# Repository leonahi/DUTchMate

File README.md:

# DUTchMate

DUTchMate helps embedded developers turn UART output and hardware-control
actions into durable evidence that humans and coding agents can inspect. Its
local Device Core Service continuously records UART while it owns a connected
backend. The CLI and service expose deterministic atomic capabilities;
clients and coding agents compose higher-level debug procedures from them.

- **Continuous evidence recording** preserves UART between client requests.
- **Audited Control** provides configured reset, boot-mode, and GPIO actions,
  with durable attempt evidence before physical dispatch.
- **Monitor** observes new evidence for a bounded duration or until a condition.
- **Interact** sends exact UART bytes once and observes a bounded response window.
- **Audited UART TX** sends standalone payloads with explicit line-ending behavior.

## What it looks like

Configure the DUT I/O voltage in the project profile and connect an RP2350-based
Debug Helper. The Enhanced backend can discover and open it during startup.
Configure the reset signal, then use separate Control and observation requests:

```bash
dutchmate devices
dutchmate start --backend enhanced
dutchmate gpio mode CTRL0 reset RESET_N \
  --mode open_drain --active-level low
dutchmate dut reset
dutchmate monitor --seconds 15
dutchmate logs --last 100
```

An illustrative Monitor result identifies its bounded evidence window:

```text
Monitor elapsed
Operation: monitor-00000000-0000-4000-8000-000000000001
Evidence: 20261025T120000Z-demo0001:0..12
```

Recording is already active before reset. A later Monitor observes only evidence
after its own start; immediate boot output remains in the session and is available
through log retrieval. These are independent atomic requests, with no dedicated
reset-and-observe workflow in Device Core.

With `[hardware.uart].tx_enabled = true`, ordinary UART interaction uses the
same service-owned connection and evidence journal:

```bash
dutchmate monitor --until BOOT_OK --timeout 10
dutchmate send PING --line-ending lf
dutchmate send --data-b64 AP8=
dutchmate interact INFO --line-ending lf --until 'DMF/1 INFO' --timeout 5
dutchmate follow                  # Ctrl-C detaches the view; recording continues
dutchmate console --line-ending lf
dutchmate sessions
dutchmate session SESSION_ID
dutchmate release                 # external same-port tool may now open the port
# Close the external tool before reacquiring.
dutchmate reacquire
```

Monitor/Interact return operation IDs and evidence ranges; finishing an operation
leaves the continuous session active. Release/reacquire records the unobserved
interval and opens a fresh timestamp segment. `capture` and `wait` are thin
Monitor aliases. New evidence uses schema v2; historical v0/v1 sessions remain
readable. The Debug Agent currently accepts schema-v1 evidence only.

Coding agents can use the CLI or service to compose procedures from Monitor,
Interact, audited UART TX, and audited reset/boot/GPIO Control. UART TX requires
the profile's TX policy to be enabled. The local stdio MCP adapter exposes the
[twelve-tool v2 catalog](docs/mcp_integration_plan.md#target-tool-catalog), including
Monitor, Interact, configured reset/boot Control and evidence retrieval. It is a
thin HTTP client of the already-running Device Core Service; it never starts the
service or acquires the serial port. Register the installed `dutchmate-mcp` or
`dutchmate mcp` command using the [developer guide](docs/developer_guide.md#register-mcp-with-a-coding-agent).

## Install

DUTchMate requires Python 3.10 or newer. The examples on this page describe the
current checkout. Install its workspace and make its commands available in the
current shell:

```bash
uv sync --all-packages
export PATH="$PWD/.venv/bin:$PATH"
```

For the published `v0.1.0` release, use either isolated-tool installer below.
That release predates the Phase 1/MCP v2 migrations; its original surface is
described in the [historical release notes](docs/releases/v0.1.0.md). The workspace
package version alone does not mean these checkout changes have been published.

```bash
uv tool install dutchmate==0.1.0
# or
pipx install dutchmate==0.1.0
```

## Quick Start

For Enhanced, set `[hardware].dut_io_voltage` in `.dutchmate/config.toml` to
the actual DUT logic voltage before opening the Debug Helper. List candidate
devices, start one backend, inspect it, and stop the service:

```bash
dutchmate devices
dutchmate start --backend enhanced
dutchmate status
dutchmate stop
```

Basic mode requires a user-selected generic USB-to-UART port. Enhanced mode can
auto-select one metadata-hinted Debug Helper; multiple candidates require an
explicit port. Run `dutchmate --help` for the complete command surface and see
the [developer guide](docs/developer_guide.md) for configuration and MCP host
registration.

For Basic, replace the start command with
`dutchmate start --backend basic --serial-port /dev/cu.EXAMPLE`, using the
actual adapter path. Select one backend at a time.

## Hardware

The **Basic** backend uses a generic TTL/logic-level USB-to-UART adapter for UART
receive and optional UART send. The **Enhanced** backend uses the RP2350-based
Raspberry Pi Pico 2 Debug Helper for UART receive/send, device timestamps,
buffer telemetry, and generic `CTRLn` control. Both feed the same host session
pipeline, but they are mutually exclusive selections; hybrid operation is not
supported.

## Contributing / Development

Start with the [current development status](docs/development_status.md), which
owns active progress and next steps. Completed work is preserved in the
[development history](docs/development_history.md). Setup and validation live
in the [developer guide](docs/developer_guide.md); the full
[documentation index](docs/README.md) and [glossary](docs/glossary.md) cover the
remaining project contracts.

The repository is a `uv` workspace. From a checkout:

```bash
uv sync --all-packages
uv run pytest
uv run ruff check .
```

## Licensing and contributions

Unless otherwise noted, DUTchMate software, firmware, protocol definitions,
documentation, scripts, and supporting tools are licensed under the
[MIT License](LICENSE).

DUTchMate-authored hardware design files under `hardware/pcb/` are licensed
under [CERN-OHL-P-2.0](LICENSES/CERN-OHL-P-2.0.txt). Third-party components
retain their respective licenses. The legacy EAGLE files and third-party CAD
assets retain their existing terms; see [LICENSE.md](LICENSE.md) for the scope
and [third-party notices](THIRD_PARTY_NOTICES.md).

The DUTchMate name, logo, and associated branding are excluded from these
grants. The MIT License and CERN-OHL-P-2.0 do not grant permission to use them
to identify or promote derivative products as official DUTchMate products.

Future pull-request commits require DCO 1.1 sign-off. See
[CONTRIBUTING.md](CONTRIBUTING.md) for the contribution and validation workflow.

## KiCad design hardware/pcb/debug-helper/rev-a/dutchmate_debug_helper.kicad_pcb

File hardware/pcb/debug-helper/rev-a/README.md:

# Debug Helper Revision A — KiCad source

This directory contains the current authoritative Rev-A KiCad design source
for the DUTchMate Debug Helper. The historical EAGLE prototype design record
is preserved separately under [legacy-eagle](../legacy-eagle/revision_a.md).
Its component references and connector assignments do not define this KiCad
implementation.

## Design sources

- `dutchmate_debug_helper.kicad_pro`: KiCad project and check settings.
- `dutchmate_debug_helper.kicad_sch`: schematic and embedded symbol definitions.
- `dutchmate_debug_helper.kicad_pcb`: board source.
- `dutchmate_debug_helper.kicad_dru`: project design rules.
- `libraries/symbols/dutchmate.kicad_sym`: project-owned logic and analog-switch
  symbol definitions, resolved through `sym-lib-table` using `${KIPRJMOD}`.

The sources use KiCad 10 format. Standard KiCad symbols and footprints must be
installed alongside the project-owned library. Keep editable sources and any
reviewed manufacturing outputs in version control; local settings, locks,
autosaves, backups, and scratch exports are ignored.

## Electrical architecture and agreed corrections

The helper uses a non-wireless Raspberry Pi Pico 2 / RP2350 module (`A1`),
with a 3.3 V helper domain, a DUT-supplied `DUT_VIO` reference of 1.8–5.0 V,
and common ground. `DUT_VIO` supplies the interface circuitry; it is not an
output for powering the DUT.

| Block | KiCad implementation |
|---|---|
| Four control outputs | `U1 SN74LV4T125`, VCC=`DUT_VIO`; `U7/U8 SN74LVC2G06` open-drain enable drivers powered by `+3.3V` |
| Control data defaults | `R14–R17`, 10 kΩ to GND on `DBG_CTRL_DATA0–3` |
| Control enable defaults | `R1–R4`, 4.7 kΩ to GND; active-low `DBG_CTRL_OE0_N–3_N` pulled to `DUT_VIO` by `R7/R6/R9/R8`, respectively, each 4.7 kΩ |
| Four event inputs | `U5 TXU0104PWR`, VCCA=`DUT_VIO`, VCCB=`+3.3V`; `R5=4.7 kΩ` pulls `DBG_INPUT_IF_EN` low |
| UART | `U2 TXU0202DCUR`, VCCA=`+3.3V`, VCCB=`DUT_VIO`; `R12=4.7 kΩ` pulls `DBG_UART_IF_EN` low |
| Series resistance | `RN3/RN4=180 Ω` for control/event channels; `RN5=22 Ω` for UART |
| Protection | `U6` on connector-side controls, `U4` on connector-side events/UART, `D1` between `DUT_VIO` and GND |

The 4.7 kΩ enable pull-downs retain compatibility with older RP2350 A2
silicon; the design does not require A4-only modules. Control data pull-downs
define the buffer inputs while Pico GPIOs are undriven. The independent `/OE`
paths determine DUT-facing Hi-Z, including open-drain release. Push-pull and
open-drain control modes still require the appropriate firmware data/enable
sequence.

### Hardware-defined DUT_VIO sense isolation

`U3 TMUX2819DSGR` is connected as follows:

| Pin | Connection |
|---|---|
| 1, SA | `DUT_VIO` |
| 2, NC | GND, as specified by the datasheet |
| 3, EN; 8, VDD | `+3.3V`, with `C16=100 nF` between VDD and GND |
| 4, GND; 9, exposed pad | GND |
| 5, SB | Intentionally unconnected |
| 6, D | `R10` divider input |
| 7, SEL | GND |

With helper power present, EN high and SEL low select SA. With VDD absent,
the switch provides powered-off isolation within its specified leakage limits.
No firmware GPIO controls this isolation. The selected switch supports DUT
signals above its 3.3 V supply within the specified signal range. See the
[TMUX2819 datasheet](https://www.ti.com/lit/ds/symlink/tmux2819.pdf).

The divider remains `R10=47 kΩ` and `R11=47 kΩ`, with `C7=10 nF` from
`DUT_VIO_SENSE` to `GNDA`. `R11` also returns to `GNDA`, connected to the
Pico's AGND pin 33. `DUT_VIO_SENSE` reaches GP28/ADC2, module pin 34. The Pico
module supplies the internal analog/common-ground connection; these are
distinct carrier-board net names, not galvanically isolated domains.

GP28 ADC sensing is provisioned in hardware but is not implemented in the
current helper firmware: there is no ADC channel setup or digital-input-buffer
configuration for GP28. Any future sensing implementation must disable its
digital input buffer. Do not infer measured voltage monitoring from this
schematic or from the hardware-defined switch enable.

### UART receive bias

```text
J1.7 / DUT_UART_TX -- RN5A 22 Ω (pad 4 → pad 1) -- U2.B2 (pin 1)
                                                     |
                                                 R13 10 kΩ
                                                     |
                                                  DUT_VIO
```

`R13` is on the translator-input side of the series resistor, on exported net
`Net-(RN5A-R1.1)`. It references `DUT_VIO`, not fixed `+3.3V`. The translated
output is `DBG_UART_RX`, from U2 pin 4 to Pico GP1. The opposite direction is
Pico GP0 / `DBG_UART_TX` to U2 pin 5, U2 pin 8 through RN5B, then
`DUT_UART_RX` at J1 pin 8. Both UART directions share U2 OE; software TX
permission does not provide independent electrical TX isolation.

## DUT connector and interface requirements

The single 2×8 `J1` is the authoritative Rev-A DUT connector. Direct legacy
EAGLE harness compatibility is not required; any legacy connection requires
an external adapter cable.

| J1 pin(s) | Net(s) | Direction relative to helper |
|---|---|---|
| 1, 2 | GND | Common |
| 3, 4, 5, 6 | `DUT_CTRL0`, `DUT_CTRL1`, `DUT_CTRL2`, `DUT_CTRL3` | Outputs |
| 7 | `DUT_UART_TX` | Input from DUT TX |
| 8 | `DUT_UART_RX` | Output to DUT RX |
| 9, 10 | `DUT_EVENT2`, `DUT_EVENT3` | Inputs |
| 11, 12 | `DUT_EVENT0`, `DUT_EVENT1` | Inputs |
| 13 | GND | Common |
| 14 | `DUT_VIO` | Reference/supply input from DUT |
| 15, 16 | GND | Common |

`DUT_CTRL0–3` must remain within the `DUT_VIO` voltage domain. In particular,
a released externally pulled-up control signal must not be pulled above
`DUT_VIO`. U1 remains the selected SN74LV4T125. Control outputs drive logic
inputs, not DUT supply loads.

`DUT_EVENT0–3` intentionally have **no helper-side pull-ups**. These temporary
debugging inputs are normally driven by spare DUT GPIOs. The DUT/developer
must supply valid logic levels. Open-drain/open-collector outputs require a
DUT-side pull-up, including an MCU internal pull-up where its electrical and
timing performance is adequate. A floating event input is not a valid event
source.

## Validation lifecycle and evidence boundaries

The KiCad Rev-A schematic/source review is complete. PCB layout, routing,
fabrication preparation, DFM checks, Gerber review and manufacturing submission
are handled manually by the hardware designer outside the coding-agent
workflow. No further repository-driven PCB/DFM review task or acceptance gate
is planned before fabrication. Source-review completion does not establish
hardware acceptance, fabrication acceptance, production readiness or Phase 1B
acceptance.

Formal hardware validation of this corrected design begins only after
manufactured KiCad Rev-A PCBs are physically available. Each manufactured-board
validation campaign must record its own board/assembly configuration, wiring,
firmware, methods and observed results. Use the same broad categories as the
historical Rev-A work, adapted to this implementation, where applicable:

- Visual inspection, board assembly/continuity checks and firmware/board
  pin-mapping consistency.
- Power rails, `DUT_VIO` checks and operation across the supported voltage range.
- Debugger-powered/DUT-unpowered and DUT-powered/debugger-unpowered behavior,
  including powered-off back-power/leakage checks.
- `U3 TMUX2819` isolation of the `DUT_VIO` sense path and its divider/filter.
- Control-channel safe startup/Hi-Z, open-drain assertion/release and push-pull
  output levels.
- Event-input behavior with valid DUT-provided levels and any DUT-side pull-ups
  required for open-drain/open-collector signals.
- UART TX/RX functionality, the corrected after-RN5A `R13` pull-up, and UART
  signal-integrity/oscilloscope measurements.
- Hot-plug/unplug behavior and translator enable/disable sequencing.
- ESD/protection-path sanity checks where measurable, and Enhanced-backend HIL
  workflows relevant to the manufactured board.

These are future validation categories, not completed checks or new acceptance
criteria. Use applicable existing specifications and procedures for limits and
acceptance conditions; do not infer results or tolerances from source review.
The GP28 firmware limitation above and deferred EVENT capture must be respected
when defining what a physical run can demonstrate.

Adapt procedural references to the single 2×8 J1 pinout, current component/net
references and corrected circuit documented above. In particular, test the
after-RN5A `R13` pull-up at `U2.B2` to `DUT_VIO`; do not copy the historical
two-connector arrangement, historical R16 references or before-R16 rework
location into a KiCad-board procedure.

The three evidence scopes remain separate:

- Historical EAGLE [validation records](../../../validation/phase1_revision_a.md)
  establish evidence only for the actual EAGLE/as-built prototype, wiring,
  parts and firmware tested. They remain useful procedural/reference material.
  Their UART oscilloscope gap remains unresolved. The legacy board may still
  serve as a functional Enhanced HIL/development fixture under
  [Phase 1 specification §4.1](../../../../docs/phase1_implementation_spec.md#41-software-sequencing-and-hardware-acceptance-boundaries);
  such use does not establish electrical acceptance. Current-board UART
  electrical follow-up belongs to the manufactured KiCad campaign above.
- The completed KiCad source review establishes that the corrected design
  source was reviewed; it is not physical-board validation.
- Future manufactured KiCad Rev-A validation supplies separate physical
  evidence required for that board. Historical acceptance is not inherited.

Current progress and the next formal hardware-validation step belong in
[development status](../../../../docs/development_status.md); dated decisions
and source-check results belong in
[development history](../../../../docs/development_history.md).

## Licensing and provenance

DUTchMate-authored design source, project metadata, and the project-owned
symbol definitions in this directory are licensed under
[CERN-OHL-P-2.0](../../../../LICENSES/CERN-OHL-P-2.0.txt).

Embedded and referenced third-party symbols, footprints, models, and other CAD
assets retain their existing terms. Standard KiCad library data retains its
upstream license and design exception. This grant does not establish ownership
of imported assets or complete the manufacturing-output provenance audit.
Do not copy embedded EAGLE libraries or other third-party CAD assets into this
project without checking their provenance and terms. See the
[hardware scope](../../README.md) and
[third-party notices](../../../../THIRD_PARTY_NOTICES.md).

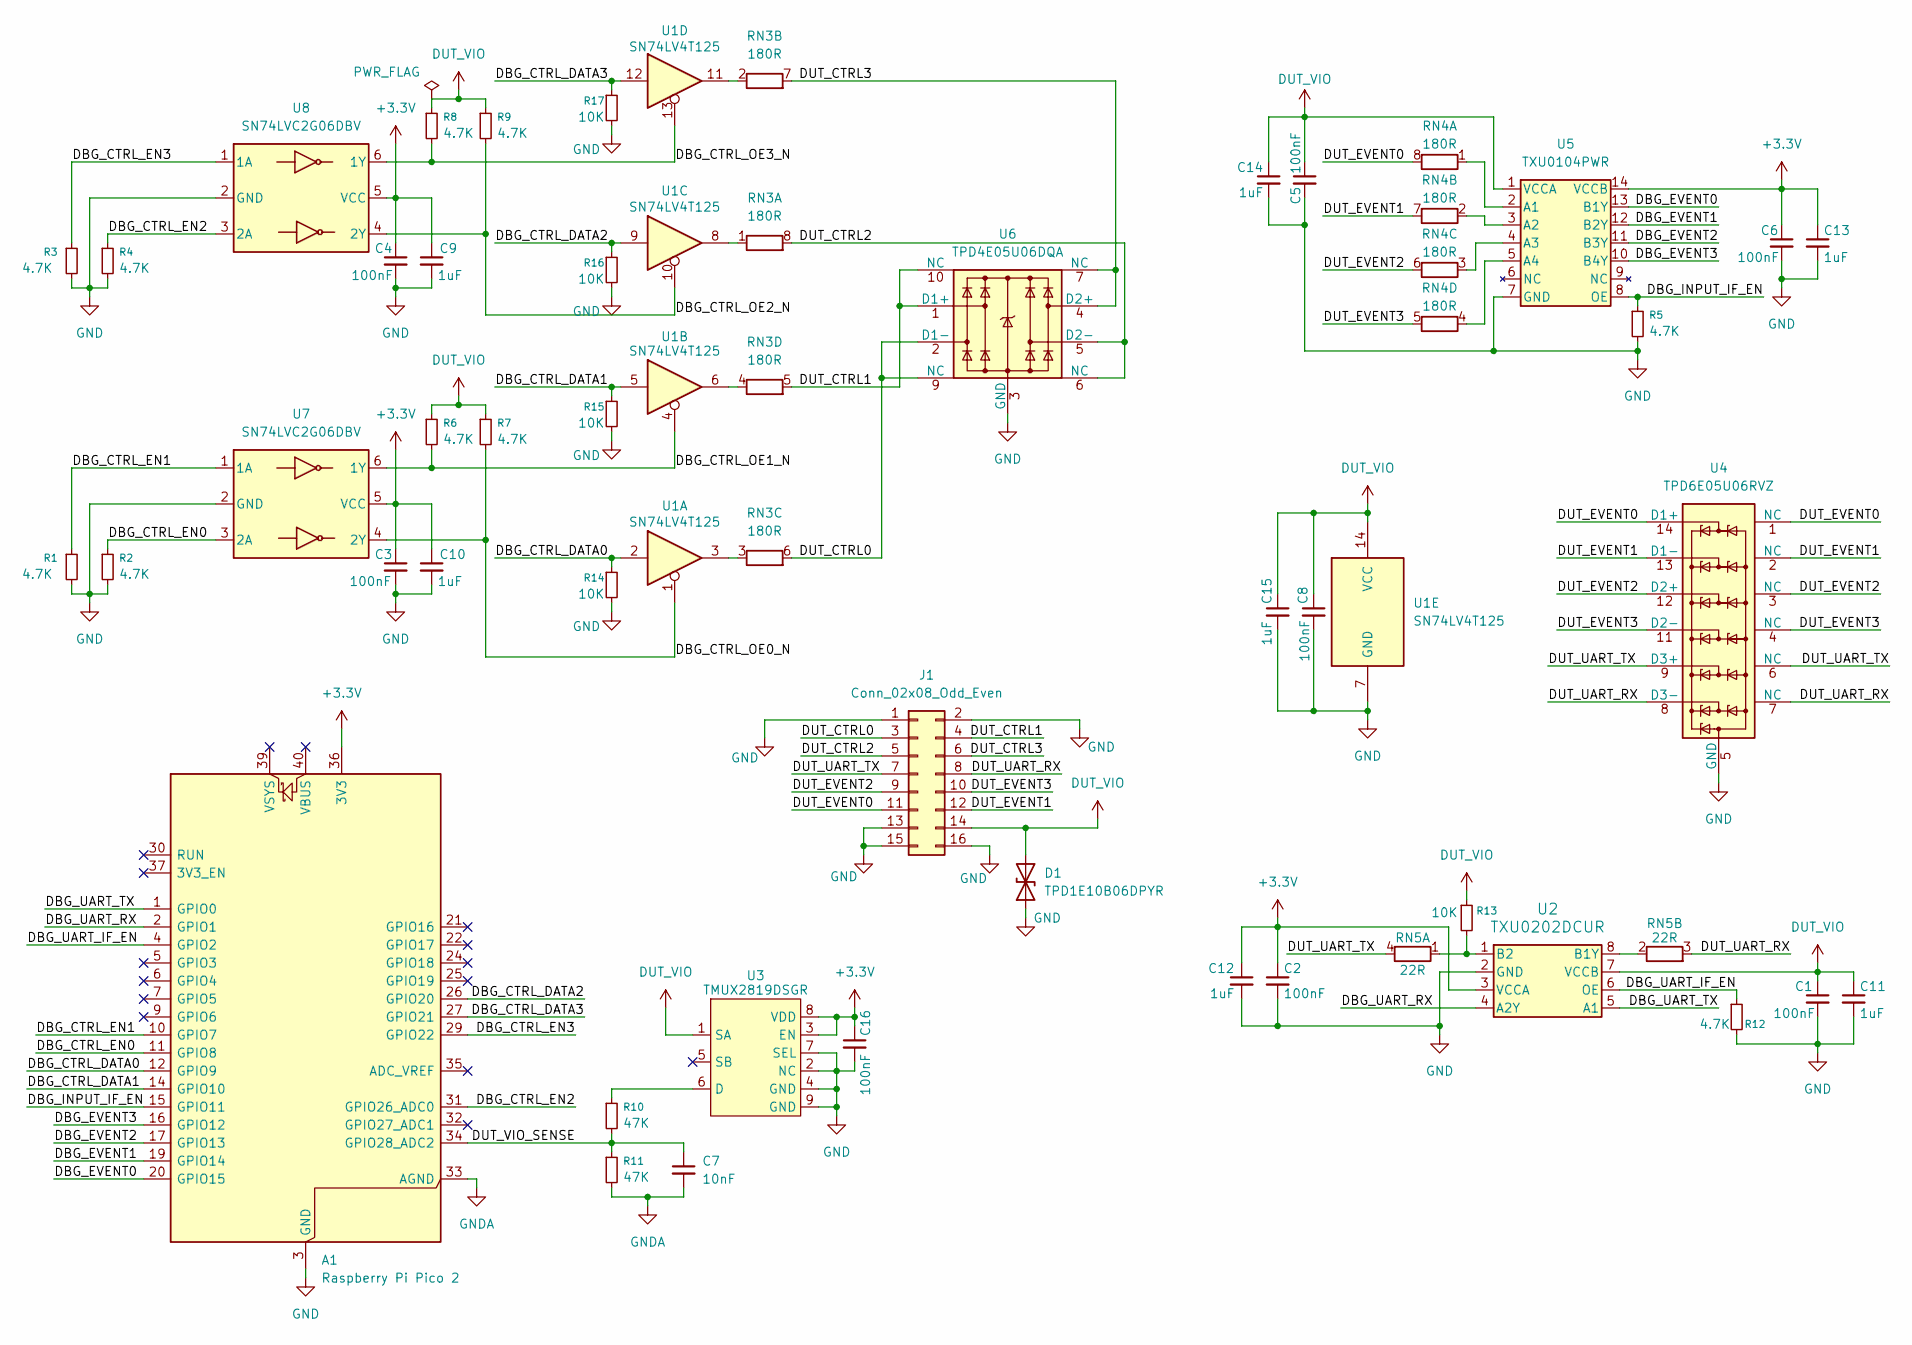
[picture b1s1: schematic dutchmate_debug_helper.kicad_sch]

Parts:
A1: Raspberry Pi Pico 2; RaspberryPi_Pico_Common_THT
C1, C2, C3, C4, C5, C6, C8, C16: 100nF; C_0603_1608Metric
C7: 10nF; C_0603_1608Metric
C9, C10, C11, C12, C13, C14, C15: 1uF; C_0603_1608Metric
D1: TPD1E10B06DPYR; Texas_DPY0002A_0.6x1mm_P0.65mm
J1: Conn_02x08_Odd_Even; PinHeader_2x08_P2.54mm_Vertical
R1, R2, R3, R4, R5, R6, R7, R8, R9, R12: 4.7K; R_0603_1608Metric
R10, R11: 47K; R_0603_1608Metric
R13, R14, R15, R16, R17: 10K; R_0603_1608Metric
RN3, RN4: 180R; R_Array_Concave_4x0603
RN5: 22R; R_Array_Concave_2x0603
U1: SN74LV4T125; TSSOP-14_4.4x5mm_P0.65mm
U2: TXU0202DCUR; VSSOP-8_2.3x2mm_P0.5mm
U3: TMUX2819DSGR; Texas_DSG0008A_WSON-8-1EP_2x2mm_P0.5mm_EP0.9x1.6mm
U4: TPD6E05U06RVZ; Texas_R-PUSON-N14
U5: TXU0104PWR; TSSOP-14_4.4x5mm_P0.65mm
U6: TPD4E05U06DQA; USON-10_2.5x1.0mm_P0.5mm
U7, U8: SN74LVC2G06DBV; SOT-23-6

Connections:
+3.3V: A1.36 (3V3), C2.1, C3.1, C4.1, C6.1, C9.1, C10.1, C12.1, C13.1, C16.1, U2.3 (VCCA), U3.3 (EN), U3.8 (VDD), U5.14 (VCCB), U7.5 (VCC), U8.5 (VCC)
/DBG_CTRL_DATA0: A1.12 (GPIO9), R14.1, U1.2
/DBG_CTRL_DATA1: A1.14 (GPIO10), R15.1, U1.5
/DBG_CTRL_DATA2: A1.26 (GPIO20), R16.1, U1.9
/DBG_CTRL_DATA3: A1.27 (GPIO21), R17.1, U1.12
/DBG_CTRL_EN0: A1.11 (GPIO8), R2.1, U7.3 (2A)
/DBG_CTRL_EN1: A1.10 (GPIO7), R1.1, U7.1 (1A)
/DBG_CTRL_EN2: A1.31 (GPIO26_ADC0), R4.1, U8.3 (2A)
/DBG_CTRL_EN3: A1.29 (GPIO22), R3.1, U8.1 (1A)
/DBG_CTRL_OE0_N: R7.2, U1.1, U7.4 (2Y)
/DBG_CTRL_OE1_N: R6.2, U1.4, U7.6 (1Y)
/DBG_CTRL_OE2_N: R9.2, U1.10, U8.4 (2Y)
/DBG_CTRL_OE3_N: R8.2, U1.13, U8.6 (1Y)
/DBG_EVENT0: A1.20 (GPIO15), U5.13 (B1Y)
/DBG_EVENT1: A1.19 (GPIO14), U5.12 (B2Y)
/DBG_EVENT2: A1.17 (GPIO13), U5.11 (B3Y)
/DBG_EVENT3: A1.16 (GPIO12), U5.10 (B4Y)
/DBG_INPUT_IF_EN: A1.15 (GPIO11), R5.1, U5.8 (OE)
/DBG_UART_IF_EN: A1.4 (GPIO2), R12.1, U2.6 (OE)
/DBG_UART_RX: A1.2 (GPIO1), U2.4 (A2Y)
/DBG_UART_TX: A1.1 (GPIO0), U2.5 (A1)
/DUT_CTRL0: J1.3, RN3.6 (R3.2), U6.2 (D1-), U6.9 (NC)
/DUT_CTRL1: J1.4, RN3.5 (R4.2), U6.1 (D1+), U6.10 (NC)
/DUT_CTRL2: J1.5, RN3.8 (R1.2), U6.5 (D2-), U6.6 (NC)
/DUT_CTRL3: J1.6, RN3.7 (R2.2), U6.4 (D2+), U6.7 (NC)
/DUT_EVENT0: J1.11, RN4.8 (R1.2), U4.1 (NC), U4.14 (D1+)
/DUT_EVENT1: J1.12, RN4.7 (R2.2), U4.2 (NC), U4.13 (D1-)
/DUT_EVENT2: J1.9, RN4.6 (R3.2), U4.3 (NC), U4.12 (D2+)
/DUT_EVENT3: J1.10, RN4.5 (R4.2), U4.4 (NC), U4.11 (D2-)
/DUT_UART_RX: J1.8, RN5.3 (R2.2), U4.7 (NC), U4.8 (D3-)
/DUT_UART_TX: J1.7, RN5.4 (R1.2), U4.6 (NC), U4.9 (D3+)
/DUT_VIO_SENSE: A1.34 (GPIO28_ADC2), C7.1, R10.2, R11.1
DUT_VIO: C1.1, C5.1, C8.1, C11.1, C14.1, C15.1, D1.2 (A2), J1.14, R6.1, R7.1, R8.1, R9.1, R13.1, U1.14 (VCC), U2.7 (VCCB), U3.1 (SA), U5.1 (VCCA)
GND: A1.3 (GND), A1.8 (GND), A1.13 (GND), A1.18 (GND), A1.23 (GND), A1.28 (GND), A1.38 (GND), C1.2, C2.2, C3.2, C4.2, C5.2, C6.2, C8.2, C9.2, C10.2, C11.2, C12.2, C13.2, C14.2, C15.2, C16.2, D1.1 (A1), J1.1, J1.2, J1.13, J1.15, J1.16, R1.2, R2.2, R3.2, R4.2, R5.2, R12.2, R14.2, R15.2, R16.2, R17.2, U1.7 (GND), U2.2 (GND), U3.2 (NC), U3.4 (GND), U3.7 (SEL), U3.9 (GND), U4.5 (GND), U4.10 (GND), U5.7 (GND), U6.3 (GND), U6.8 (GND), U7.2 (GND), U8.2 (GND)
GNDA: A1.33 (AGND), C7.2, R11.2
unnamed: RN3.1 (R1.1), U1.8
unnamed: RN3.2 (R2.1), U1.11
unnamed: RN3.3 (R3.1), U1.3
unnamed: RN3.4 (R4.1), U1.6
unnamed: RN4.1 (R1.1), U5.2 (A1)
unnamed: RN4.2 (R2.1), U5.3 (A2)
unnamed: RN4.3 (R3.1), U5.4 (A3)
unnamed: RN4.4 (R4.1), U5.5 (A4)
unnamed: R13.2, RN5.1 (R1.1), U2.1 (B2)
unnamed: RN5.2 (R2.1), U2.8 (B1Y)
unnamed: R10.1, U3.6 (D)

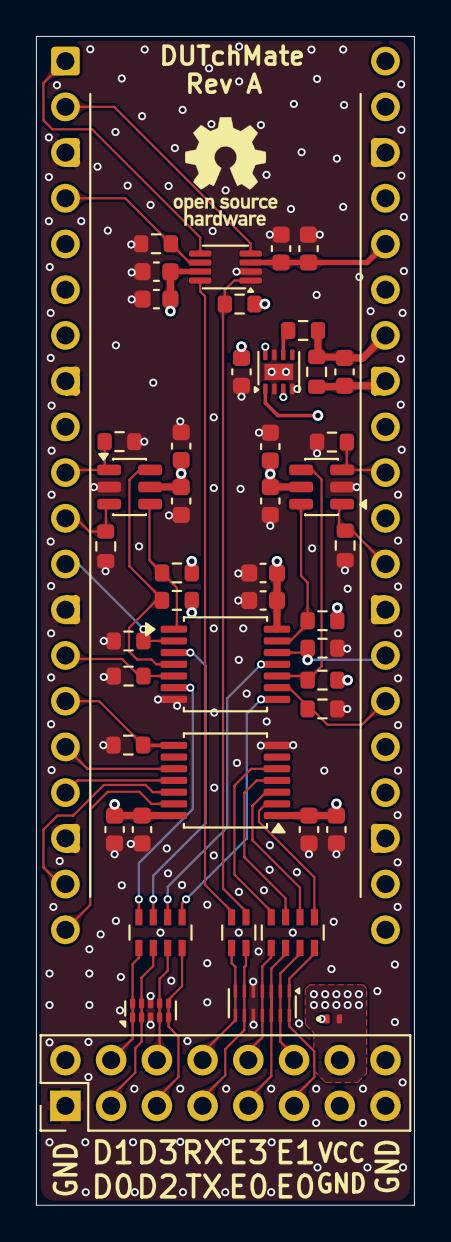
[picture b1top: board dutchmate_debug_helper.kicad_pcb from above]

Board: 4 copper layers, 21.0 x 64.9 mm, 47 parts (0 on the bottom side), 46 nets.
